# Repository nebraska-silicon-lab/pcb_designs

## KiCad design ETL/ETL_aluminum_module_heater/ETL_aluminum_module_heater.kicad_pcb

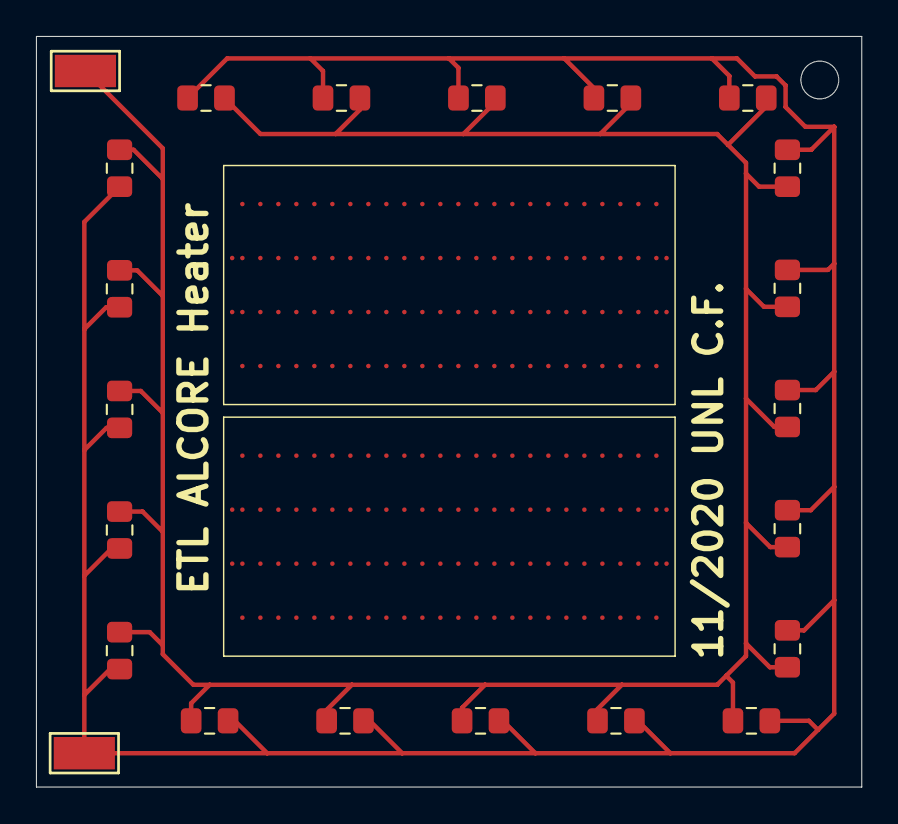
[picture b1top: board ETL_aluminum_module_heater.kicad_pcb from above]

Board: 2 copper layers, 45.9 x 41.7 mm, 24 parts (0 on the bottom side), 2 nets.

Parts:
J1, J2: Conn_01x01; TestPoint_Keystone_5015_Micro-Minature
R1, R2, R3, R4, R5, R6, R7, R8, R9, R10, R11, R12, R13, R14, R15, R16, R17, R18, R19, R20: 50; R_0805_2012Metric_Pad1.15x1.40mm_HandSolder
SEN2, SEN5: ROC1_sans_wirebonds

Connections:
/GND: J2.1, R1.1, R2.1, R3.1, R4.1, R5.1, R6.1, R7.1, R8.1, R9.1, R10.1, R11.2, R12.2, R13.2, R14.2, R15.2, R16.2, R17.2, R18.2, R19.2, R20.2
/VCC: J1.1, R1.2, R2.2, R3.2, R4.2, R5.2, R6.2, R7.2, R8.2, R9.2, R10.2, R11.1, R12.1, R13.1, R14.1, R15.1, R16.1, R17.1, R18.1, R19.1, R20.1

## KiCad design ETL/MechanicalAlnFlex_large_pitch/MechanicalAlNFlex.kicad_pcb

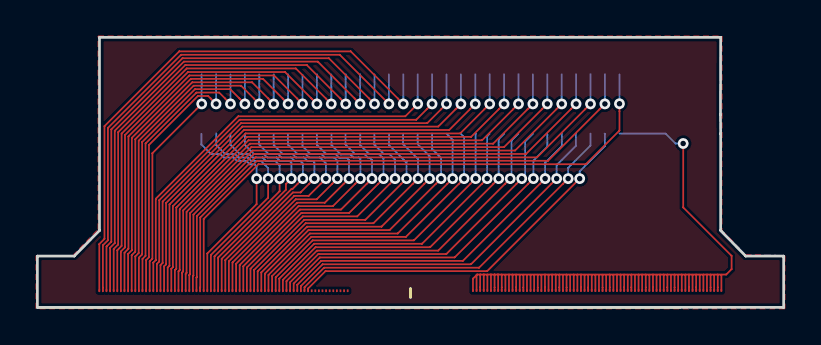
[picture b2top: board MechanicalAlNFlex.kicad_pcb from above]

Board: 2 copper layers, 41.5 x 15.0 mm, 3 parts (0 on the bottom side), 60 nets.

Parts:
J1: Conn_02x30_Odd_Even; SAMTEC_FTE-130-01-G-DV-EC
J2, J3: Conn_02x35_Top_Bottom; ETROC_70pad_100x150um_200um_pitch

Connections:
/COM: J1.1, J3.1, J3.2, J3.3, J3.4, J3.5, J3.6, J3.7, J3.8, J3.9, J3.10, J3.11, J3.12, J3.13, J3.14, J3.15, J3.16, J3.17, J3.18, J3.19, J3.20, J3.21, J3.22, J3.23, J3.24, J3.25, J3.26, J3.27, J3.28, J3.29, J3.30, J3.31, J3.32, J3.33, J3.34, J3.35, J3.36, J3.37, J3.38, J3.39, J3.40, J3.41, J3.42, J3.43, J3.44, J3.45, J3.46, J3.47, J3.48, J3.49, J3.50, J3.51, J3.52, J3.53, J3.54, J3.55, J3.56, J3.57, J3.58, J3.59, J3.60, J3.61, J3.62, J3.63, J3.64, J3.65, J3.66, J3.67, J3.68, J3.69, J3.70
/P1: J1.60, J2.15
/P2: J1.58, J2.14
/P3: J1.56, J2.13
/P4: J1.54, J2.12
/P5: J1.52, J2.11
/P6: J1.50, J2.10
/P7: J1.48, J2.9
/P8: J1.46, J2.8
/P9: J1.44, J2.7
/P10: J1.42, J2.6
/P11: J1.40, J2.5
/P12: J1.38, J2.4
/P13: J1.36, J2.3
/P14: J1.34, J2.2
/P15: J1.32, J2.1
/P16: J1.30, J2.16
/P17: J1.28, J2.17
/P18: J1.26, J2.18
/P19: J1.24, J2.19
/P20: J1.22, J2.20
/P21: J1.20, J2.21
/P22: J1.18, J2.22
/P23: J1.16, J2.23
/P24: J1.14, J2.24
/P25: J1.12, J2.25
/P26: J1.10, J2.26
/P27: J1.8, J2.27
/P28: J1.6, J2.28
/P29: J1.4, J2.29
/P30: J1.2, J2.30
/P31: J1.59, J2.31
/P32: J1.57, J2.32
/P33: J1.55, J2.33
/P34: J1.53, J2.34
/P35: J1.51, J2.35
/P36: J1.49, J2.36
/P37: J1.47, J2.37
/P38: J1.45, J2.38
/P39: J1.43, J2.39
/P40: J1.41, J2.40
/P41: J1.39, J2.41
/P42: J1.37, J2.42
/P43: J1.35, J2.43
/P44: J1.33, J2.44
/P45: J1.31, J2.45
/P46: J1.29, J2.46
/P47: J1.27, J2.47
/P48: J1.25, J2.48
/P49: J1.23, J2.49
/P50: J1.21, J2.50
/P51: J1.19, J2.51
/P52: J1.17, J2.52
/P53: J1.15, J2.53
/P54: J1.13, J2.54
/P55: J1.11, J2.55
/P56: J1.9, J2.56
/P57: J1.7, J2.57
/P58: J1.5, J2.58
/P59: J1.3, J2.59

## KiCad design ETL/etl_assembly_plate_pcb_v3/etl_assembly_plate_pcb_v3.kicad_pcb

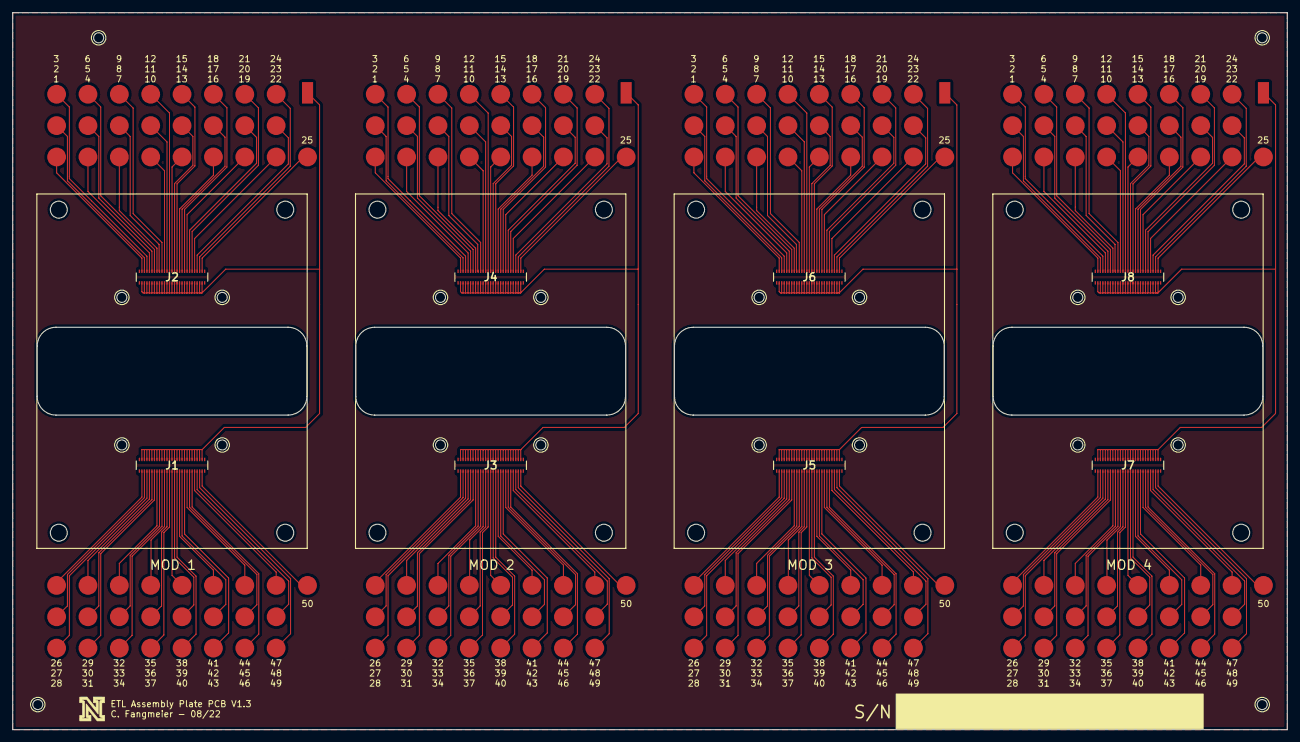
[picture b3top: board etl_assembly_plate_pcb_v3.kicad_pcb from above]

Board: 2 copper layers, 203.2 x 114.3 mm, 212 parts (0 on the bottom side), 59 nets.

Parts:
J1, J2, J3, J4, J5, J6, J7, J8: WP7B-P050VA1-R8000; WP7BP050VA1R8000
TP1, TP2, TP3, TP4, TP5, TP6, TP7, TP8, TP9, TP10, TP11, TP12, TP13, TP14, TP15, TP16, TP17, TP18, TP19, TP20, TP21, TP22, TP23, TP24, TP25, TP26, TP27, TP28, TP29, TP30, TP31, TP32, TP33, TP34, TP35, TP36, TP37, TP38, TP39, TP40, TP41, TP42, TP43, TP44, TP45, TP46, TP47, TP48, TP49, TP50, TP52, TP53, TP54, TP55, TP56, TP57, TP58, TP59, TP60, TP61, TP62, TP63, TP64, TP65, TP66, TP67, TP68, TP69, TP70, TP71, TP72, TP73, TP74, TP75, TP76, TP77, TP78, TP79, TP80, TP81, TP82, TP83, TP84, TP85, TP86, TP87, TP88, TP89, TP90, TP91, TP92, TP93, TP94, TP95, TP96, TP97, TP98, TP99, TP100, TP101, TP103, TP104, TP105, TP106, TP107, TP108, TP109, TP110, TP111, TP112, TP113, TP114, TP115, TP116, TP117, TP118, TP119, TP120, TP121, TP122, TP123, TP124, TP125, TP126, TP127, TP128, TP129, TP130, TP131, TP132, TP133, TP134, TP135, TP136, TP137, TP138, TP139, TP140, TP141, TP142, TP143, TP144, TP145, TP146, TP147, TP148, TP149, TP150, TP151, TP152, TP154, TP155, TP156, TP157, TP158, TP159, TP160, TP161, TP162, TP163, TP164, TP165, TP166, TP167, TP168, TP169, TP170, TP171, TP172, TP173, TP174, TP175, TP176, TP177, TP178, TP179, TP180, TP181, TP182, TP183, TP184, TP185, TP186, TP187, TP188, TP189, TP190, TP191, TP192, TP193, TP194, TP195, TP196, TP197, TP198, TP199, TP200, TP201, TP202, TP203: TestPoint; TestPoint_Pad_D3.0mm
TP51, TP102, TP153, TP204: TestPoint; Keystone-5084-Test-Point

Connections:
/D01: J1.1, J3.1, J5.1, J7.1, TP26.1, TP77.1, TP128.1, TP179.1
/D02: J1.3, J3.3, J5.3, J7.3, TP27.1, TP78.1, TP129.1, TP180.1
/D03: J1.5, J3.5, J5.5, J7.5, TP28.1, TP79.1, TP130.1, TP181.1
/D04: J1.7, J3.7, J5.7, J7.7, TP29.1, TP80.1, TP131.1, TP182.1
/D05: J1.9, J3.9, J5.9, J7.9, TP30.1, TP81.1, TP132.1, TP183.1
/D06: J1.11, J3.11, J5.11, J7.11, TP31.1, TP82.1, TP133.1, TP184.1
/D07: J1.13, J3.13, J5.13, J7.13, TP32.1, TP83.1, TP134.1, TP185.1
/D08: J1.15, J3.15, J5.15, J7.15, TP33.1, TP84.1, TP135.1, TP186.1
/D09: J1.17, J3.17, J5.17, J7.17, TP34.1, TP85.1, TP136.1, TP187.1
/D10: J1.19, J3.19, J5.19, J7.19, TP35.1, TP86.1, TP137.1, TP188.1
/D11: J1.21, J3.21, J5.21, J7.21, TP36.1, TP87.1, TP138.1, TP189.1
/D12: J1.23, J3.23, J5.23, J7.23, TP37.1, TP88.1, TP139.1, TP190.1
/D13: J1.25, J3.25, J5.25, J7.25, TP38.1, TP89.1, TP140.1, TP191.1
/D14: J1.27, J3.27, J5.27, J7.27, TP39.1, TP90.1, TP141.1, TP192.1
/D15: J1.29, J3.29, J5.29, J7.29, TP40.1, TP91.1, TP142.1, TP193.1
/D16: J1.31, J3.31, J5.31, J7.31, TP41.1, TP92.1, TP143.1, TP194.1
/D17: J1.33, J3.33, J5.33, J7.33, TP42.1, TP93.1, TP144.1, TP195.1
/D18: J1.35, J3.35, J5.35, J7.35, TP43.1, TP94.1, TP145.1, TP196.1
/D19: J1.37, J3.37, J5.37, J7.37, TP44.1, TP95.1, TP146.1, TP197.1
/D20: J1.39, J3.39, J5.39, J7.39, TP45.1, TP96.1, TP147.1, TP198.1
/D21: J1.41, J3.41, J5.41, J7.41, TP46.1, TP97.1, TP148.1, TP199.1
/D22: J1.43, J3.43, J5.43, J7.43, TP47.1, TP98.1, TP149.1, TP200.1
/D23: J1.45, J3.45, J5.45, J7.45, TP48.1, TP99.1, TP150.1, TP201.1
/D24: J1.47, J3.47, J5.47, J7.47, TP49.1, TP100.1, TP151.1, TP202.1
/D25: J1.49, J3.49, J5.49, J7.49, TP50.1, TP101.1, TP152.1, TP203.1
/D26: J2.2, J4.2, J6.2, J8.2, TP1.1, TP52.1, TP103.1, TP154.1
/D27: J2.4, J4.4, J6.4, J8.4, TP2.1, TP53.1, TP104.1, TP155.1
/D28: J2.6, J4.6, J6.6, J8.6, TP3.1, TP54.1, TP105.1, TP156.1
/D29: J2.8, J4.8, J6.8, J8.8, TP4.1, TP55.1, TP106.1, TP157.1
/D30: J2.10, J4.10, J6.10, J8.10, TP5.1, TP56.1, TP107.1, TP158.1
/D31: J2.12, J4.12, J6.12, J8.12, TP6.1, TP57.1, TP108.1, TP159.1
/D32: J2.14, J4.14, J6.14, J8.14, TP7.1, TP58.1, TP109.1, TP160.1
/D33: J2.16, J4.16, J6.16, J8.16, TP8.1, TP59.1, TP110.1, TP161.1
/D34: J2.18, J4.18, J6.18, J8.18, TP9.1, TP60.1, TP111.1, TP162.1
/D35: J2.20, J4.20, J6.20, J8.20, TP10.1, TP61.1, TP112.1, TP163.1
/D36: J2.22, J4.22, J6.22, J8.22, TP11.1, TP62.1, TP113.1, TP164.1
/D37: J2.24, J4.24, J6.24, J8.24, TP12.1, TP63.1, TP114.1, TP165.1
/D38: J2.26, J4.26, J6.26, J8.26, TP13.1, TP64.1, TP115.1, TP166.1
/D39: J2.28, J4.28, J6.28, J8.28, TP14.1, TP65.1, TP116.1, TP167.1
/D40: J2.30, J4.30, J6.30, J8.30, TP15.1, TP66.1, TP117.1, TP168.1
/D41: J2.32, J4.32, J6.32, J8.32, TP16.1, TP67.1, TP118.1, TP169.1
/D42: J2.34, J4.34, J6.34, J8.34, TP17.1, TP68.1, TP119.1, TP170.1
/D43: J2.36, J4.36, J6.36, J8.36, TP18.1, TP69.1, TP120.1, TP171.1
/D44: J2.38, J4.38, J6.38, J8.38, TP19.1, TP70.1, TP121.1, TP172.1
/D45: J2.40, J4.40, J6.40, J8.40, TP20.1, TP71.1, TP122.1, TP173.1
/D46: J2.42, J4.42, J6.42, J8.42, TP21.1, TP72.1, TP123.1, TP174.1
/D47: J2.44, J4.44, J6.44, J8.44, TP22.1, TP73.1, TP124.1, TP175.1
/D48: J2.46, J4.46, J6.46, J8.46, TP23.1, TP74.1, TP125.1, TP176.1
/D49: J2.48, J4.48, J6.48, J8.48, TP24.1, TP75.1, TP126.1, TP177.1
/D50: J2.50, J4.50, J6.50, J8.50, TP25.1, TP76.1, TP127.1, TP178.1
/P1: J1.2, J1.4, J1.6, J1.8, J1.10, J1.12, J1.14, J1.16, J1.18, J1.20, J1.22, J1.24, J1.26, J1.28, J1.30, J1.32, J1.34, J1.36, J1.38, J1.40, J1.42, J1.44, J1.46, J1.48, J1.50, J2.1, J2.3, J2.5, J2.7, J2.9, J2.11, J2.13, J2.15, J2.17, J2.19, J2.21, J2.23, J2.25, J2.27, J2.29, J2.31, J2.33, J2.35, J2.37, J2.39, J2.41, J2.43, J2.45, J2.47, J2.49, J3.2, J3.4, J3.6, J3.8, J3.10, J3.12, J3.14, J3.16, J3.18, J3.20, J3.22, J3.24, J3.26, J3.28, J3.30, J3.32, J3.34, J3.36, J3.38, J3.40, J3.42, J3.44, J3.46, J3.48, J3.50, J4.1, J4.3, J4.5, J4.7, J4.9, J4.11, J4.13, J4.15, J4.17, J4.19, J4.21, J4.23, J4.25, J4.27, J4.29, J4.31, J4.33, J4.35, J4.37, J4.39, J4.41, J4.43, J4.45, J4.47, J4.49, J5.2, J5.4, J5.6, J5.8, J5.10, J5.12, J5.14, J5.16, J5.18, J5.20, J5.22, J5.24, J5.26, J5.28, J5.30, J5.32, J5.34, J5.36, J5.38, J5.40, J5.42, J5.44, J5.46, J5.48, J5.50, J6.1, J6.3, J6.5, J6.7, J6.9, J6.11, J6.13, J6.15, J6.17, J6.19, J6.21, J6.23, J6.25, J6.27, J6.29, J6.31, J6.33, J6.35, J6.37, J6.39, J6.41, J6.43, J6.45, J6.47, J6.49, J7.2, J7.4, J7.6, J7.8, J7.10, J7.12, J7.14, J7.16, J7.18, J7.20, J7.22, J7.24, J7.26, J7.28, J7.30, J7.32, J7.34, J7.36, J7.38, J7.40, J7.42, J7.44, J7.46, J7.48, J7.50, J8.1, J8.3, J8.5, J8.7, J8.9, J8.11, J8.13, J8.15, J8.17, J8.19, J8.21, J8.23, J8.25, J8.27, J8.29, J8.31, J8.33, J8.35, J8.37, J8.39, J8.41, J8.43, J8.45, J8.47, J8.49, TP51.1, TP102.1, TP153.1, TP204.1
unnamed: J1.MP1, J3.MP1, J5.MP1, J7.MP1
unnamed: J1.MP2, J3.MP2, J5.MP2, J7.MP2
unnamed: J1.MP3, J3.MP3, J5.MP3, J7.MP3
unnamed: J1.MP4, J3.MP4, J5.MP4, J7.MP4
unnamed: J2.MP1, J4.MP1, J6.MP1, J8.MP1
unnamed: J2.MP2, J4.MP2, J6.MP2, J8.MP2
unnamed: J2.MP3, J4.MP3, J6.MP3, J8.MP3
unnamed: J2.MP4, J4.MP4, J6.MP4, J8.MP4
